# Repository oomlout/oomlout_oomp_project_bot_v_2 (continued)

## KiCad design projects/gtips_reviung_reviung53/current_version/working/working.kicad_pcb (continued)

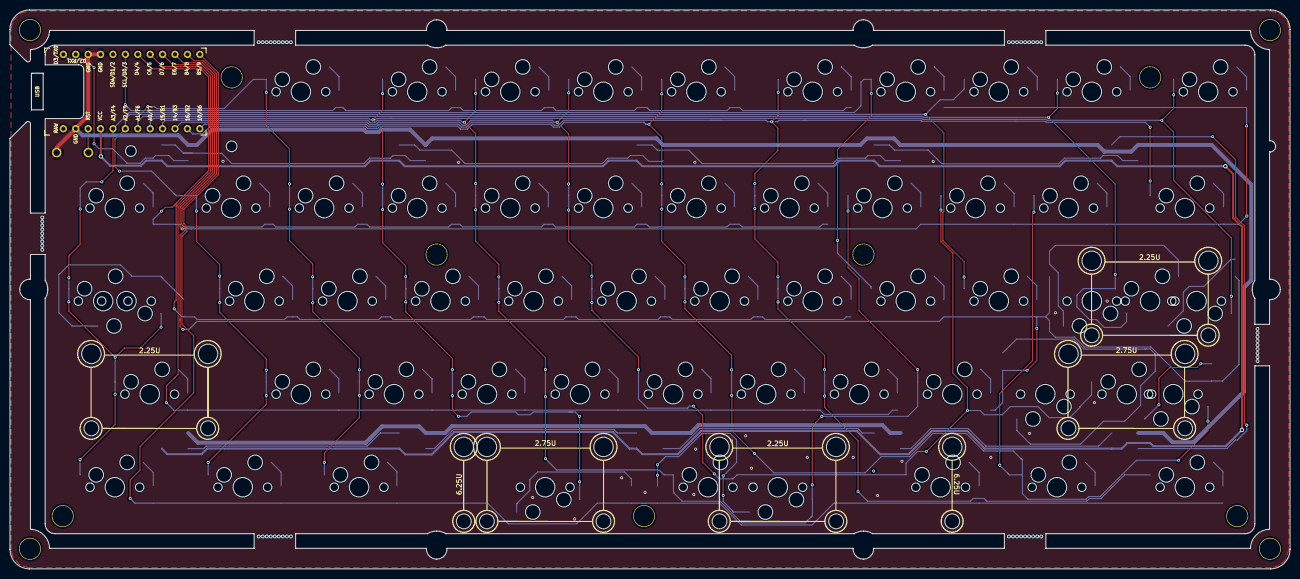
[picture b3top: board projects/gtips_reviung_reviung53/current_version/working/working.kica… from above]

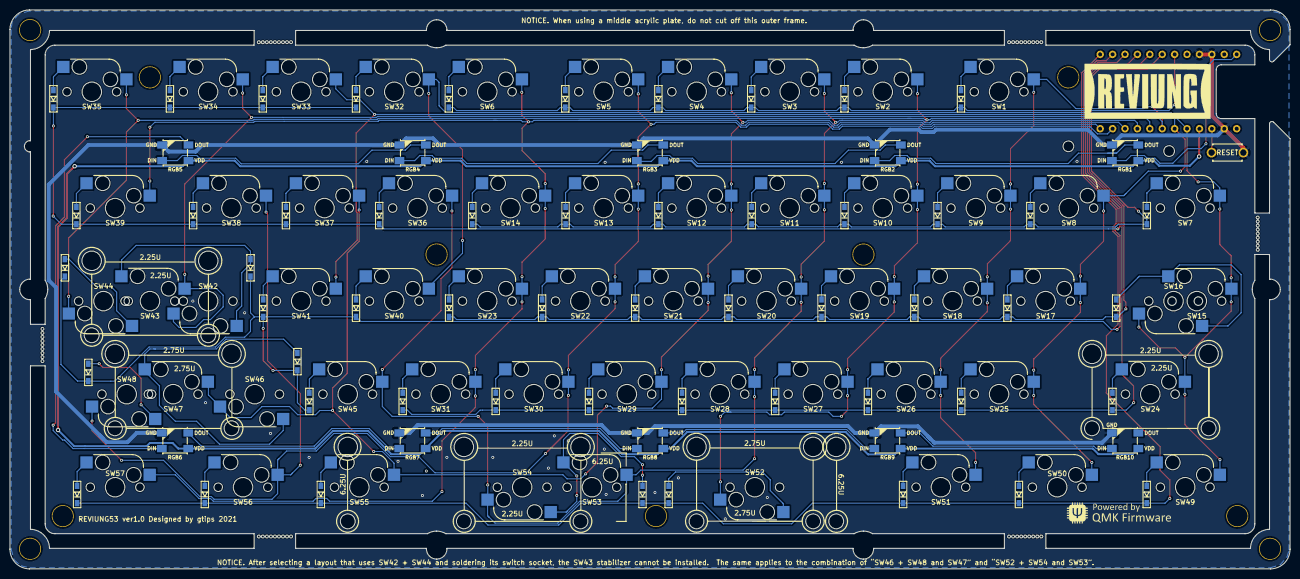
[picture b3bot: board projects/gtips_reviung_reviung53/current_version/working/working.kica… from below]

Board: 2 copper layers, 262.0 x 114.4 mm, 130 parts (64 on the bottom side), 81 nets.

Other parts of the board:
Ref**: Val**; HOLE_2.2mm
Ref**#2: Val**; HOLE_2.2mm
breakaway: Stamp_Holes_7.5mm
breakaway#2, breakaway#3, breakaway#4, breakaway#5, breakaway#6: Stamp_Holes_7.5mm

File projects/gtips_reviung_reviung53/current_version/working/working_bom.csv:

"Id";"Designator";"Footprint";"Quantity";"Designation";"Supplier and ref";
1;"SW1";"MXOnly-1U-Hotswap";1;"1";;;
2;"SW2";"MXOnly-1U-Hotswap";1;"2";;;
3;"SW3";"MXOnly-1U-Hotswap";1;"3";;;
4;"SW4";"MXOnly-1U-Hotswap";1;"4";;;
5;"SW5";"MXOnly-1U-Hotswap";1;"5";;;
6;"SW6";"MXOnly-1U-Hotswap";1;"6";;;
7;"SW7,SW39,SW49,SW57";"MXOnly-1.5U-Hotswap";4;"1.5U";;;
8;"SW8";"MXOnly-1U-Hotswap";1;"Q";;;
9;"SW9";"MXOnly-1U-Hotswap";1;"W";;;
10;"SW10";"MXOnly-1U-Hotswap";1;"E";;;
11;"SW11";"MXOnly-1U-Hotswap";1;"R";;;
12;"SW12";"MXOnly-1U-Hotswap";1;"T";;;
13;"SW13";"MXOnly-1U-Hotswap";1;"Y";;;
14;"SW14";"MXOnly-1U-Hotswap";1;"U";;;
15;"SW16,SW48";"MXOnly-1.75U-Hotswap";2;"1.75U";;;
16;"SW17";"MXOnly-1U-Hotswap";1;"A";;;
17;"SW18";"MXOnly-1U-Hotswap";1;"S";;;
18;"SW19";"MXOnly-1U-Hotswap";1;"D";;;
19;"SW20";"MXOnly-1U-Hotswap";1;"F";;;
20;"SW21";"MXOnly-1U-Hotswap";1;"G";;;
21;"SW22";"MXOnly-1U-Hotswap";1;"H";;;
22;"SW23";"MXOnly-1U-Hotswap";1;"J";;;
23;"SW24,SW43";"MXOnly-2.25U-Hotswap-ReversedStabilizers";2;"2.25U";;;
24;"SW25";"MXOnly-1U-Hotswap";1;"Z";;;
25;"SW26";"MXOnly-1U-Hotswap";1;"X";;;
26;"SW27";"MXOnly-1U-Hotswap";1;"C";;;
27;"SW28";"MXOnly-1U-Hotswap";1;"V";;;
28;"SW29";"MXOnly-1U-Hotswap";1;"B";;;
29;"SW30";"MXOnly-1U-Hotswap";1;"N";;;
30;"SW31";"MXOnly-1U-Hotswap";1;"M";;;
31;"SW32";"MXOnly-1U-Hotswap";1;"7";;;
32;"SW33";"MXOnly-1U-Hotswap";1;"8";;;
33;"SW34";"MXOnly-1U-Hotswap";1;"9";;;
34;"SW35,SW37";"MXOnly-1U-Hotswap";2;"0";;;
35;"SW36";"MXOnly-1U-Hotswap";1;"I";;;
36;"SW38";"MXOnly-1U-Hotswap";1;"P";;;
37;"SW40";"MXOnly-1U-Hotswap";1;"K";;;
38;"SW41";"MXOnly-1U-Hotswap";1;"L";;;
39;"SW42,SW46";"MXOnly-1U-Hotswap";2;"1U";;;
40;"SW44,SW50,SW51,SW55,SW56,SW15";"MXOnly-1.25U-Hotswap";6;"1.25U";;;
41;"SW53";"MXOnly-6.25U-Hotswap-ReversedStabilizers";1;"6.25U";;;
42;"SW54";"MXOnly-2.25U-Hotswap";1;"2.25U";;;
43;"U1";"ProMicro";1;"ProMicro";;;
44;"SW52";"MXOnly-2.75U-Hotswap";1;"2.75U";;;
45;"SW45";"MXOnly-1U-Hotswap";1;"<";;;
46;"REF**,REF**,REF**,REF**,REF**,REF**,REF**,REF**,REF**,REF**,REF**";"HOLE_4.2mm";11;"HOLE_4.2mm";;;
47;"breakaway,breakaway,breakaway,breakaway,breakaway,breakaway";"Stamp_Holes_7.5mm";6;"Stamp_Holes_7.5mm";;;
48;"SW47";"MXOnly-2.75U-Hotswap-ReversedStabilizers";1;"2.75U";;;
49;"D1,D2,D3,D4,D5,D6,D7,D8,D9,D10,D11,D12,D13,D14,D15,D16,D17,D18,D19,D20,D21,D22,D23,D24,D25,D26,D27,D28,D29,D30,D31,D32,D33,D34,D35,D36,D37,D38,D39,D40,D41,D42,D43,D44,D45,D46,D47,D48,D49,D50,D51,D52,D53";"D3_SMD_1side";53;"1N4148W";;;
50;"RESET1";"ResetSW_1side";1;"SW_PUSH";;;
51;"RGB1,RGB2,RGB3,RGB4,RGB5,RGB6,RGB7,RGB8,RGB9,RGB10";"LED_WS2812B_PLCC4_5.0x5.0mm_P3.2mm_BigFoot";10;"WS2812B";;;
52;"G***";"reviung-logo";1;"LOGO";;;
53;"G***";"QMK-x4-ver1";1;"LOGO";;;
